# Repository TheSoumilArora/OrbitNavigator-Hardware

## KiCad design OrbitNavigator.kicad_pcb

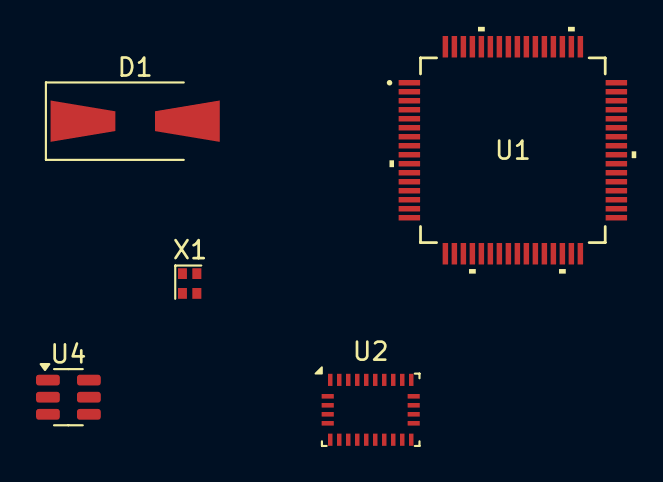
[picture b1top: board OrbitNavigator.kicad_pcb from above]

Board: 2 copper layers, 5 parts (0 on the bottom side), 2 nets, no tracks yet.

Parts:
D1: SM6T6V8A; D_SMA-SMB_Universal_Handsoldering
U1: STM32G474RET6; STM32G474RE
U2: BNO055; LGA-28_5.2x3.8mm_P0.5mm
U4: USBLC6-2SC6; SOT-23-6
X1: ASCO; Oscillator_SMD_Abracon_ASCO-4Pin_1.6x1.2mm

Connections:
GND: D1.2 (A2), U2.2 (GND), U2.15 (GNDIO), U2.16 (GNDIO), U2.25 (GNDIO), U4.2 (GND), X1.2 (GND)
VDD: U2.3 (VDD), U2.5 (PS1), U2.6 (PS0), U2.28 (VDDIO), X1.1 (Tri-State), X1.4 (VDD)

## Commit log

2024-12-17 Added : STM32G474RE Schematic
2024-12-22 Sensor and MCU Schematic Done
    Added
